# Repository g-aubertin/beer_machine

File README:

### how to install and configure ###

1)make
2)sudo make install
3)edit configuration file in /opt/beer_machine/config.ini
4)enable daemon file with 'sudo systemctl enable beer_machine' and reboot the device

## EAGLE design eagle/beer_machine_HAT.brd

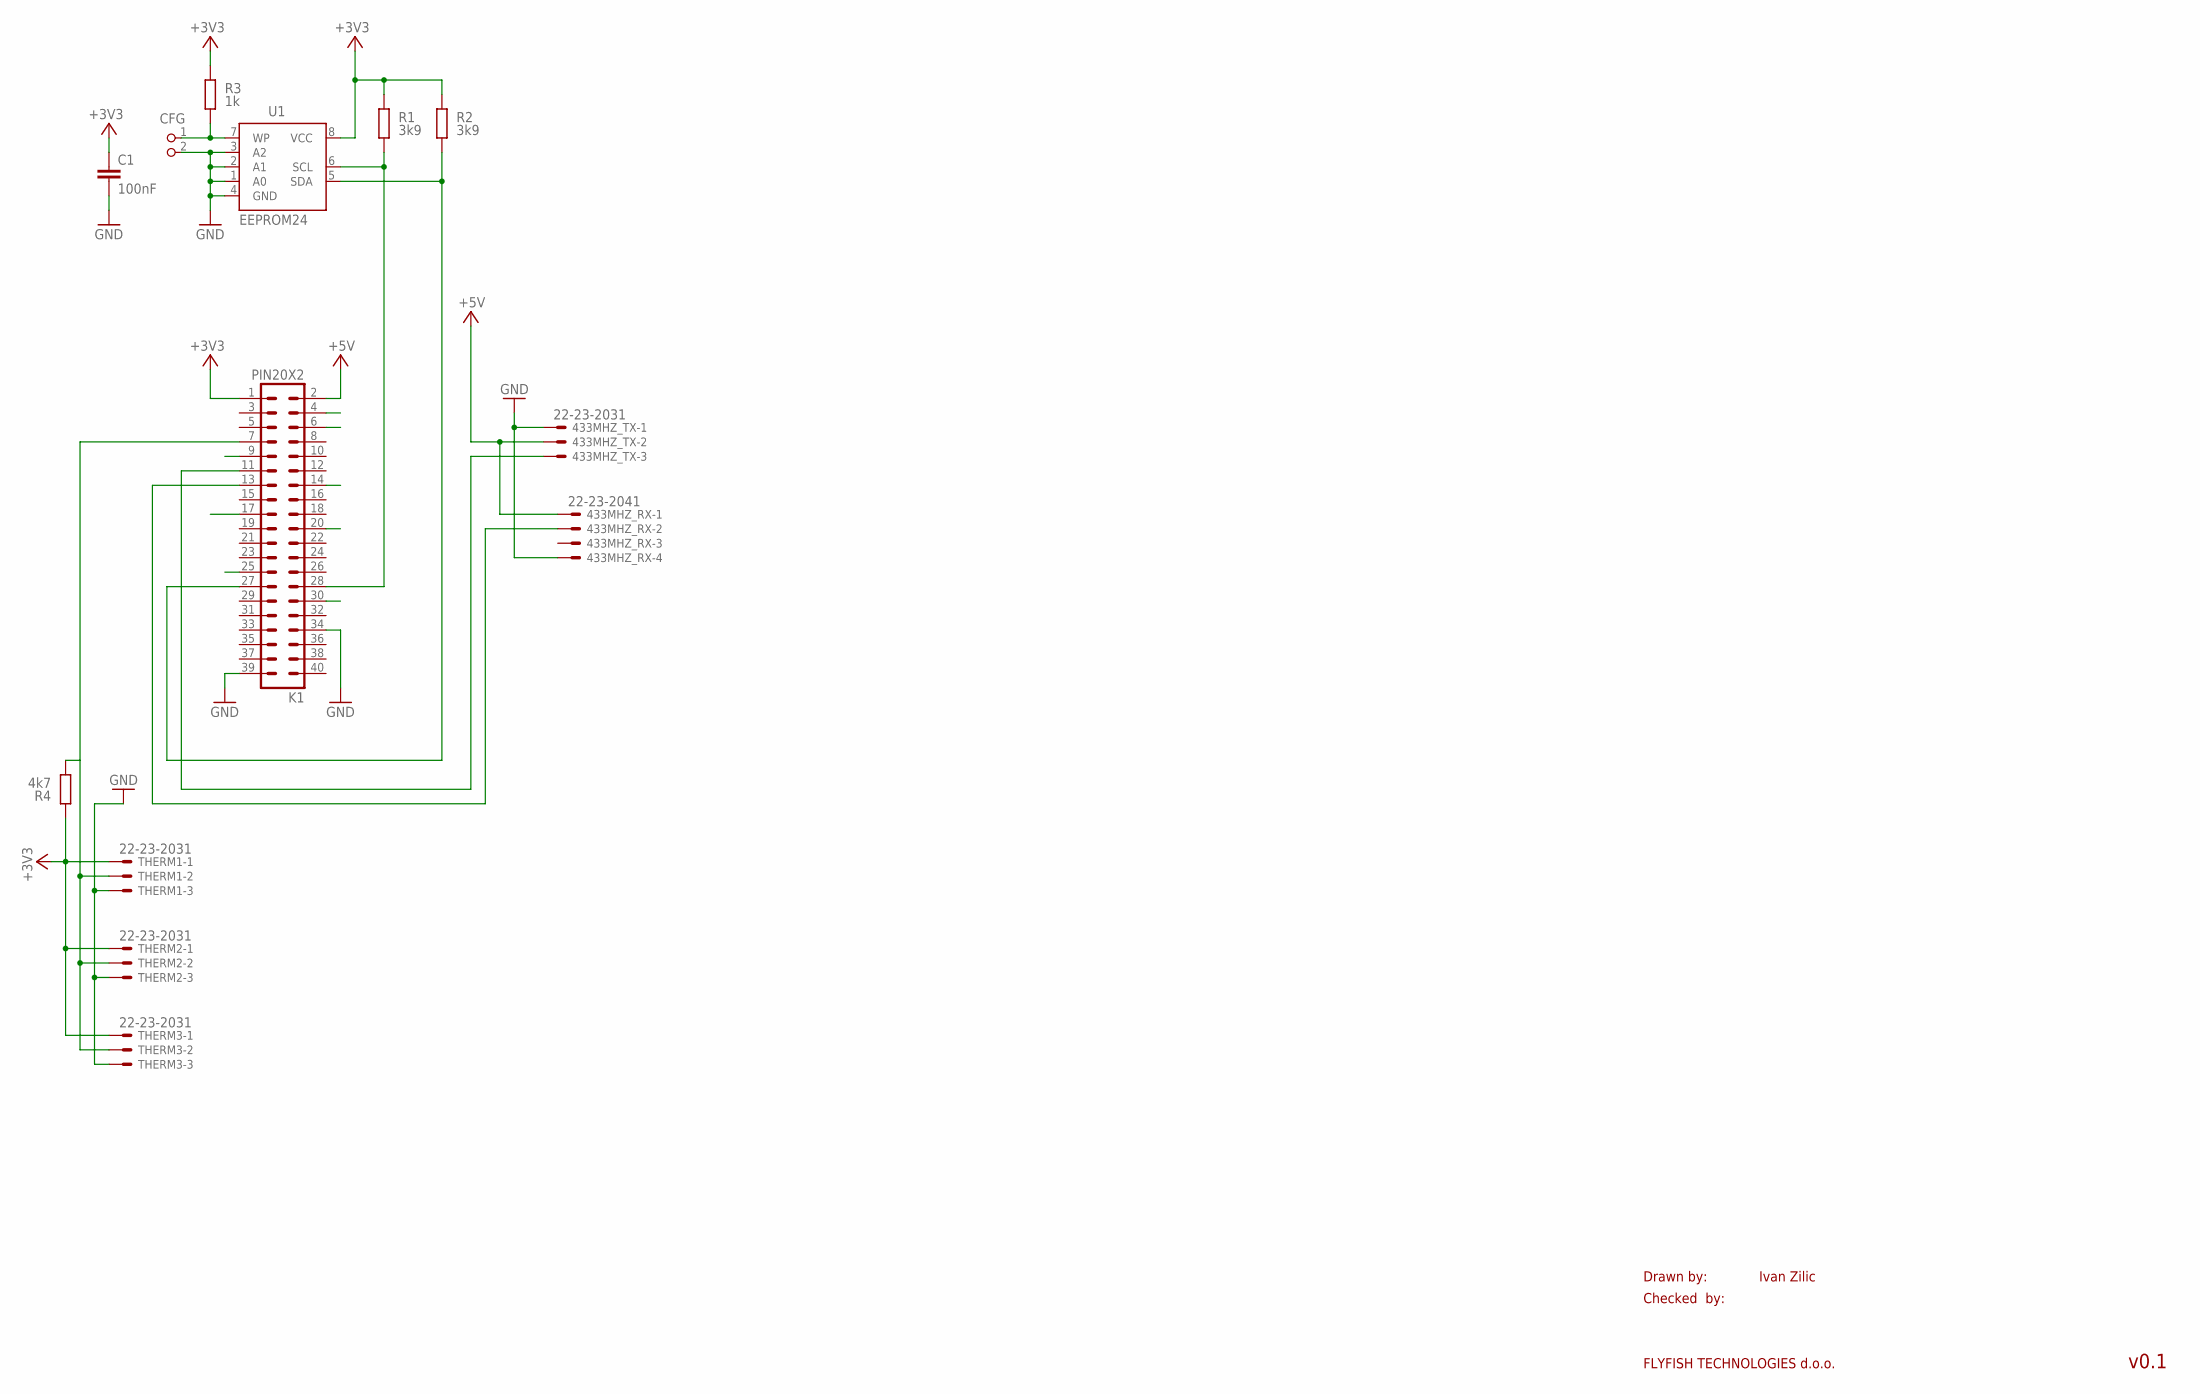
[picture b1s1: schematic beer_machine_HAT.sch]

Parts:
433MHZ_RX: 22-23-2041
433MHZ_TX: 22-23-2031
C1: 100nF; C0805K
CFG: PIN2_100; PIN_W_2
K1: PIN20X2; PIN_20X2
R1, R2: 3k9; M0805; TOLERANCE 5%
R3: 1k; M0805; TOLERANCE 5%
R4: 4k7; M0805; TOLERANCE 5%
THERM1, THERM2, THERM3: 22-23-2031
U1: EEPROM24; SOIC8

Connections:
+3V3: C1.1, K1.1, R1.2, R2.2, R3.2, R4.2, THERM1.1, THERM2.1, THERM3.1, U1.8 (VCC)
+5V: 433MHZ_RX.1, 433MHZ_TX.2, K1.2
GND: 433MHZ_RX.4, 433MHZ_TX.1, C1.2, CFG.2, K1.34, K1.39, THERM1.3, THERM2.3, THERM3.3, U1.1 (A0), U1.2 (A1), U1.3 (A2), U1.4 (GND)
unnamed: K1.28, R1.1, U1.6 (SCL)
unnamed: K1.27, R2.1, U1.5 (SDA)
unnamed: CFG.1, R3.1, U1.7 (WP)
unnamed: K1.7, R4.1, THERM1.2, THERM2.2, THERM3.2
unnamed: 433MHZ_TX.3, K1.11
unnamed: 433MHZ_RX.2, K1.13

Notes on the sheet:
Drawn by:
Checked by:
FLYFISH TECHNOLOGIES d.o.o.
Ivan Zilic
v0.1

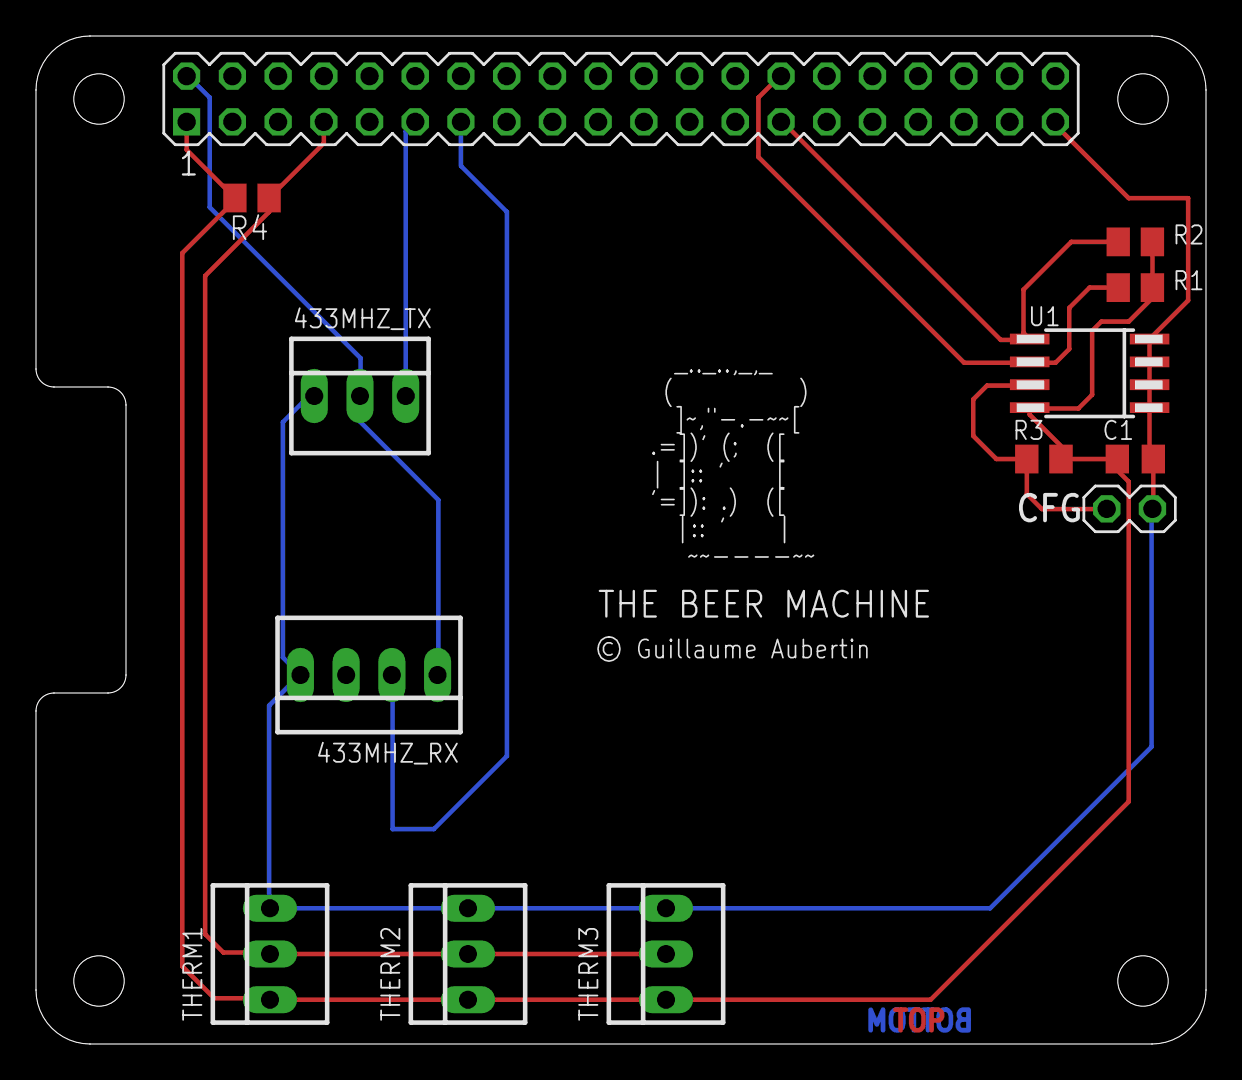
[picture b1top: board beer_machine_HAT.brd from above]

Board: 2 copper layers, 65.0 x 56.0 mm, 13 parts (0 on the bottom side), 9 nets.

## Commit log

2016-12-14 removing extra line in systemd service file
2016-12-14 fixing typo in 433_send
2016-12-14 adding eagle PCB files
    Raspberry Pi HAT design files (board and schematics) for
    eagle.
2016-12-14 removing Android notification script
2016-12-14 433_send: adding GPL V3 header
2016-12-14 433_send: removing unused variable
2017-01-09 README : adding systemctl command
2017-01-24 web: first nodejs implementation webui.py to be removed later
2017-01-25 temp
2017-01-25 nodejs: refactoring ejs files and adding new batch page
2017-01-26 temp implementation of body-parser
2017-01-31 nodejs: adding database manipulation and new batch creation
2017-02-15 bootstrap WIP
2017-03-19 bootstrap migration : first draft
2017-03-25 new_batch: moving to bootstrap
2017-03-28 boostrap: CDNs: fix for dropdowns
    adding jquery and fixing BS links. Needed to make dropdown work
2017-03-28 webpage: clean-up
    - removing unused ejs files
    - moving navbar to header file and sidebar to new file
    - adding database read before loading new_batch page
2017-03-28 webpage: adding start/shutdown button
    and some cleanup
2017-03-29 webpage: fixing undefined reference in new_batch
2017-03-29 nodejs: adding system page
    - express routing
    - static system data display (to be changed)
2017-03-29 nodejs: clean-up
    removing unused files
2017-03-29 sqlite3: adding sample db
    for testing
2017-03-29 webpage: chartist example
2017-03-29 webpage: highchart example
2017-03-29 chartist: removing Xaxis grid
2017-04-03 beer_machine.py : refactoring WIP
2017-06-02 WIP 2
2017-06-07 adding threading for temp control
2017-09-05 server.js: cleaning the batch selection in / GET
2017-09-05 adding sample db and removing gitignore for .db
2017-09-05 beer_machine.py: removing 433mhz code for now
2017-09-07 adding test_mode to python daemon
2017-09-07 quick hack for test mode
2017-10-31 beer_machine.py: fixing threading issues
    - reworking the worker thread usage
    - exception handling for SIGINT during recv()
2017-10-31 beer_machine.py: add state machine
    Also align the server with proper status and display red cross when daemon is 'stopped'.
2017-10-31 fixes in sql database handling
    - handle table creation and table_list from python only
    - send CREATE message with data when creating a new batch
    - now using time.ctime() instead of datetime
2017-10-31 cosmetic & comment fixes
2017-10-31 monitoring rework WIP
2017-11-02 nodejs: aesthetic & comment changes
2017-11-07 implement per batch temperature logging
    - send batch name to the daemon for proper database insert
    - add post routing for monitoring page
2018-01-17 temp commit for rework
2018-01-24 database rework initial draft
2018-02-09 config file clean-up
2018-02-09 beer_db: close connector before return
2018-02-09 nodejs: cosmetic changes
2018-03-06 node: adding gentelella template
2018-03-07 gentelella: wip
2018-03-14 node: temporary hack to display template page
2018-07-22 remove old web-ui
2018-07-22 remove RF tools
2018-07-22 ui template clean-up
2018-07-22 ui template cleanup part 2
2018-07-22 fix import
2018-07-22 ui template clean-up part 3
2018-07-30 index clean-up
2018-07-30 removing 3rd row for now
2018-07-30 fixing status response in daemon
2018-07-30 enabling stop/start button for single batch
2018-08-13 some changes to fit archlinux
2018-08-13 beer_machine.py: poll for exit signal during sleep
2018-08-14 re-indent server.js with emacs
2018-08-14 html: use db to plot values
2018-08-14 nodejs: moving chart javascript to separate file
    also re-indent files with emacs
2018-08-14 chartjs: adding dynamic data push
2019-01-11 beer_db: generate json file for charting
2019-01-14 highchart.js: working implementation with json data file
2019-01-14 beer_db: generate json file in public/ dir
2019-01-14 highchart: fix datapoints limit & minor graphic fix
2019-01-21 fix charting and database filling
2019-01-24 nodejs: clean-up views directory
2019-01-28 refactoring for new_batch page
2019-01-29 new batch fix
2019-01-30 update .gitignore with .pyc, .json, node install directory
2019-02-04 update sqlite3 version for node 11
2019-02-05 fix socket timing
    on slow systems (like rpi zero), we need to take a break before sending
    2 consecutive commands on the socket, or the receiver will consider it as one
    whole command.
2019-02-05 fix one-wire config
2019-02-05 add systemd services
2019-02-10 change sampling frequency to 30s
2019-02-10 fix systemd for raspbian
2019-02-25 adding TODO list for v0.2
2019-04-06 README update
2019-04-06 removing old systemd service
2019-04-06 433: clean-up
2019-05-20 js: use offline scripts
2019-05-20 add new db function to get data about current batch

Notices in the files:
eagle/beer_machine_HAT.brd:
© Guillaume Aubertin
